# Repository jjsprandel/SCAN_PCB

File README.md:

# 

Welcome to the **SCAN** repository! Below, you will find all the necessary information, from hardware design to software documentation.

---

## GitHub Workflows Status 🔧

Here are the current statuses of our GitHub workflows:

| Workflow Name            | Status                                  |
| ------------------------ | --------------------------------------- |
| **CI - Build**            |  |
| **Docker - Test Build**   |  |

- **CI - Build**: Ensures the project builds successfully.
- **CI - Tests**: Runs all unit and integration tests to ensure everything is working as expected.
- **Docker - Test Build**: Attempts Docker Build upon changes to the Dockerfile.

---

## Table of Contents 📚
- [💡 Overview](#overview)
- [🔧 Hardware Design](#hardware-design)
- [💻 Software](#software)
- [🔨 Build Instructions](#build-instructions)
- [📑 Documentation](#documentation)
- [⚙️ License](#license)

---

## 💡 Overview
 **SCAN** is a low-cost, IoT-driven kiosk system designed to provide real-time analytics based on check-in and check-out information. By integrating NFC-based authentication, real-time data processing, and a user-friendly interface, SCAN provides users with a near-effortless check-in experience and provides facilities with actionable insights for improving operations. SCAN is able to track attendance and provide detailed analytics on occupancy trends, peak usage hours, and visit durations. These insights are accessible to administrator and facility managers via SCAN’s web application, which can provide them with the necessary statistics to allocate resources efficiently, optimize staffing, and improve user experiences.

---

## 🔧 Hardware Design
<details>
  <summary><strong>📡 Schematic</strong></summary>

  Below is the schematic of the hardware design:

  **Key Features**:
  - Feature 1
  - Feature 2
  - Feature 3

  Additional hardware files can be found in the [hardware directory](hardware_design).

</details>

<details>
  <summary><strong>🔌 PCB Design</strong></summary>

  Here's the PCB design layout:

  **Important Notes**:
  - Note about the PCB.
  - Power considerations.
  - Any important design choices.

</details>

---

## 💻 Software
<details>
  <summary><strong>💾 Firmware Overview</strong></summary>

  The firmware is designed to work with the hardware for controlling the device. You can find the code [here](path/to/firmware).

  **Key Libraries Used**:
  - Library 1
  - Library 2

</details>

<details>
  <summary><strong>📦 Installation Guide</strong></summary>

  Follow these steps to install the firmware:
  
  1. Step 1
  2. Step 2
  3. Step 3

  Detailed instructions are available in the [installation guide](link_to_guide).

</details>

---

## 🔨 Build Instructions

<details>
  <summary><strong>🛠️ Build Setup</strong></summary>

  To build the project, follow these steps:

  1. Clone the repository:
     ```bash
     git clone https://github.com/jjsprandel/SCAN.git
     ```
  2. Connect your ESP32 to your computer using USB-C. The Docker container is designed to automatically recognize the device and use port 4000 to communicate to the ESP32 for flashing.
  3. Reopen Visual Studio Code in Container. This step requires having the Docker VS Code extension installed on your host machine. 
  4. Within the container, on first run, configure the ESP-IDF extension from the list of commands that come with the ESP-IDF extension.
     4a. Select "Use existing setup."
     4b. The extension should automatically find the right tool paths and folders. Select the configuration option with the auto-filled paths.
  5. Compile the firmware:
     ```bash
     idf.py build
     ```  
      5a. Alternatively, click the wrench button at the bottom of VS Code to build.
  6. Flash the firmware:
     ```bash
     idf.py --port 'rfc2217://host.docker.internal:4000?ign_set_control' flash
     ```
      6a. Alternatively, click the lightning button at the bottom of VS Code to flash.

  **Tips**:
  - Ensure your system meets the requirements listed in the [build prerequisites](link_to_prerequisites).
  - If you encounter issues, check the [troubleshooting guide](link_to_troubleshooting).

</details>

---

## 📑 Documentation
<details>
  <summary><strong>📝 API Documentation</strong></summary>

  - **[API Reference](link_to_api_reference)**: Detailed API usage and function descriptions.
  - **[Hardware Docs](link_to_hardware_docs)**: Documentation on hardware design.

</details>

<details>
  <summary><strong>📚 Additional Resources</strong></summary>

  - **[Project Wiki](link_to_wiki)**: Explore the project wiki for more in-depth articles.
  - **[User Manual](link_to_user_manual)**: Comprehensive user guide for operation.

</details>

---

## 🔌 Dependencies

This project has the following dependencies that need to be installed:

### **Hardware Dependencies:**
- **KiCad Version**: 8.0.6 (required for schematic and PCB design)
  - Download from [KiCad official website](https://kicad.org/download/).
  
### **Software Dependencies:**
- **USB Drivers**: For proper communication with the hardware, ensure that the appropriate USB drivers are installed.
  - For Windows, you can download and install the **[CP210x USB to UART Bridge VCP drivers](https://www.silabs.com/developer-tools/usb-to-uart-bridge-vcp-drivers?tab=downloads)**.
  - For Linux, you should have the necessary drivers already built into the kernel, but check the [driver documentation](https://www.silabs.com/community/interface/usb-bridges) for troubleshooting.

- **Docker Desktop**: Required to run the ESP-IDF containerized environment.
  - Download from **[Docker Desktop website](https://www.docker.com/products/docker-desktop)**.
  - Follow the installation instructions for your operating system.
  
### **Development Tools:**
- **[Visual Studio Code](https://code.visualstudio.com/)**: Recommended IDE for editing the firmware code.

- **[Git](https://git-scm.com/)**: Version control system.

---

## ⚙️ License
SCAN © 2025 is licensed under Creative Commons Attribution-NonCommercial-NoDerivatives 4.0 International. To view a copy of this license, visit https://creativecommons.org/licenses/by-nc-nd/4.0/ or see the [LICENSE](LICENSE) file.

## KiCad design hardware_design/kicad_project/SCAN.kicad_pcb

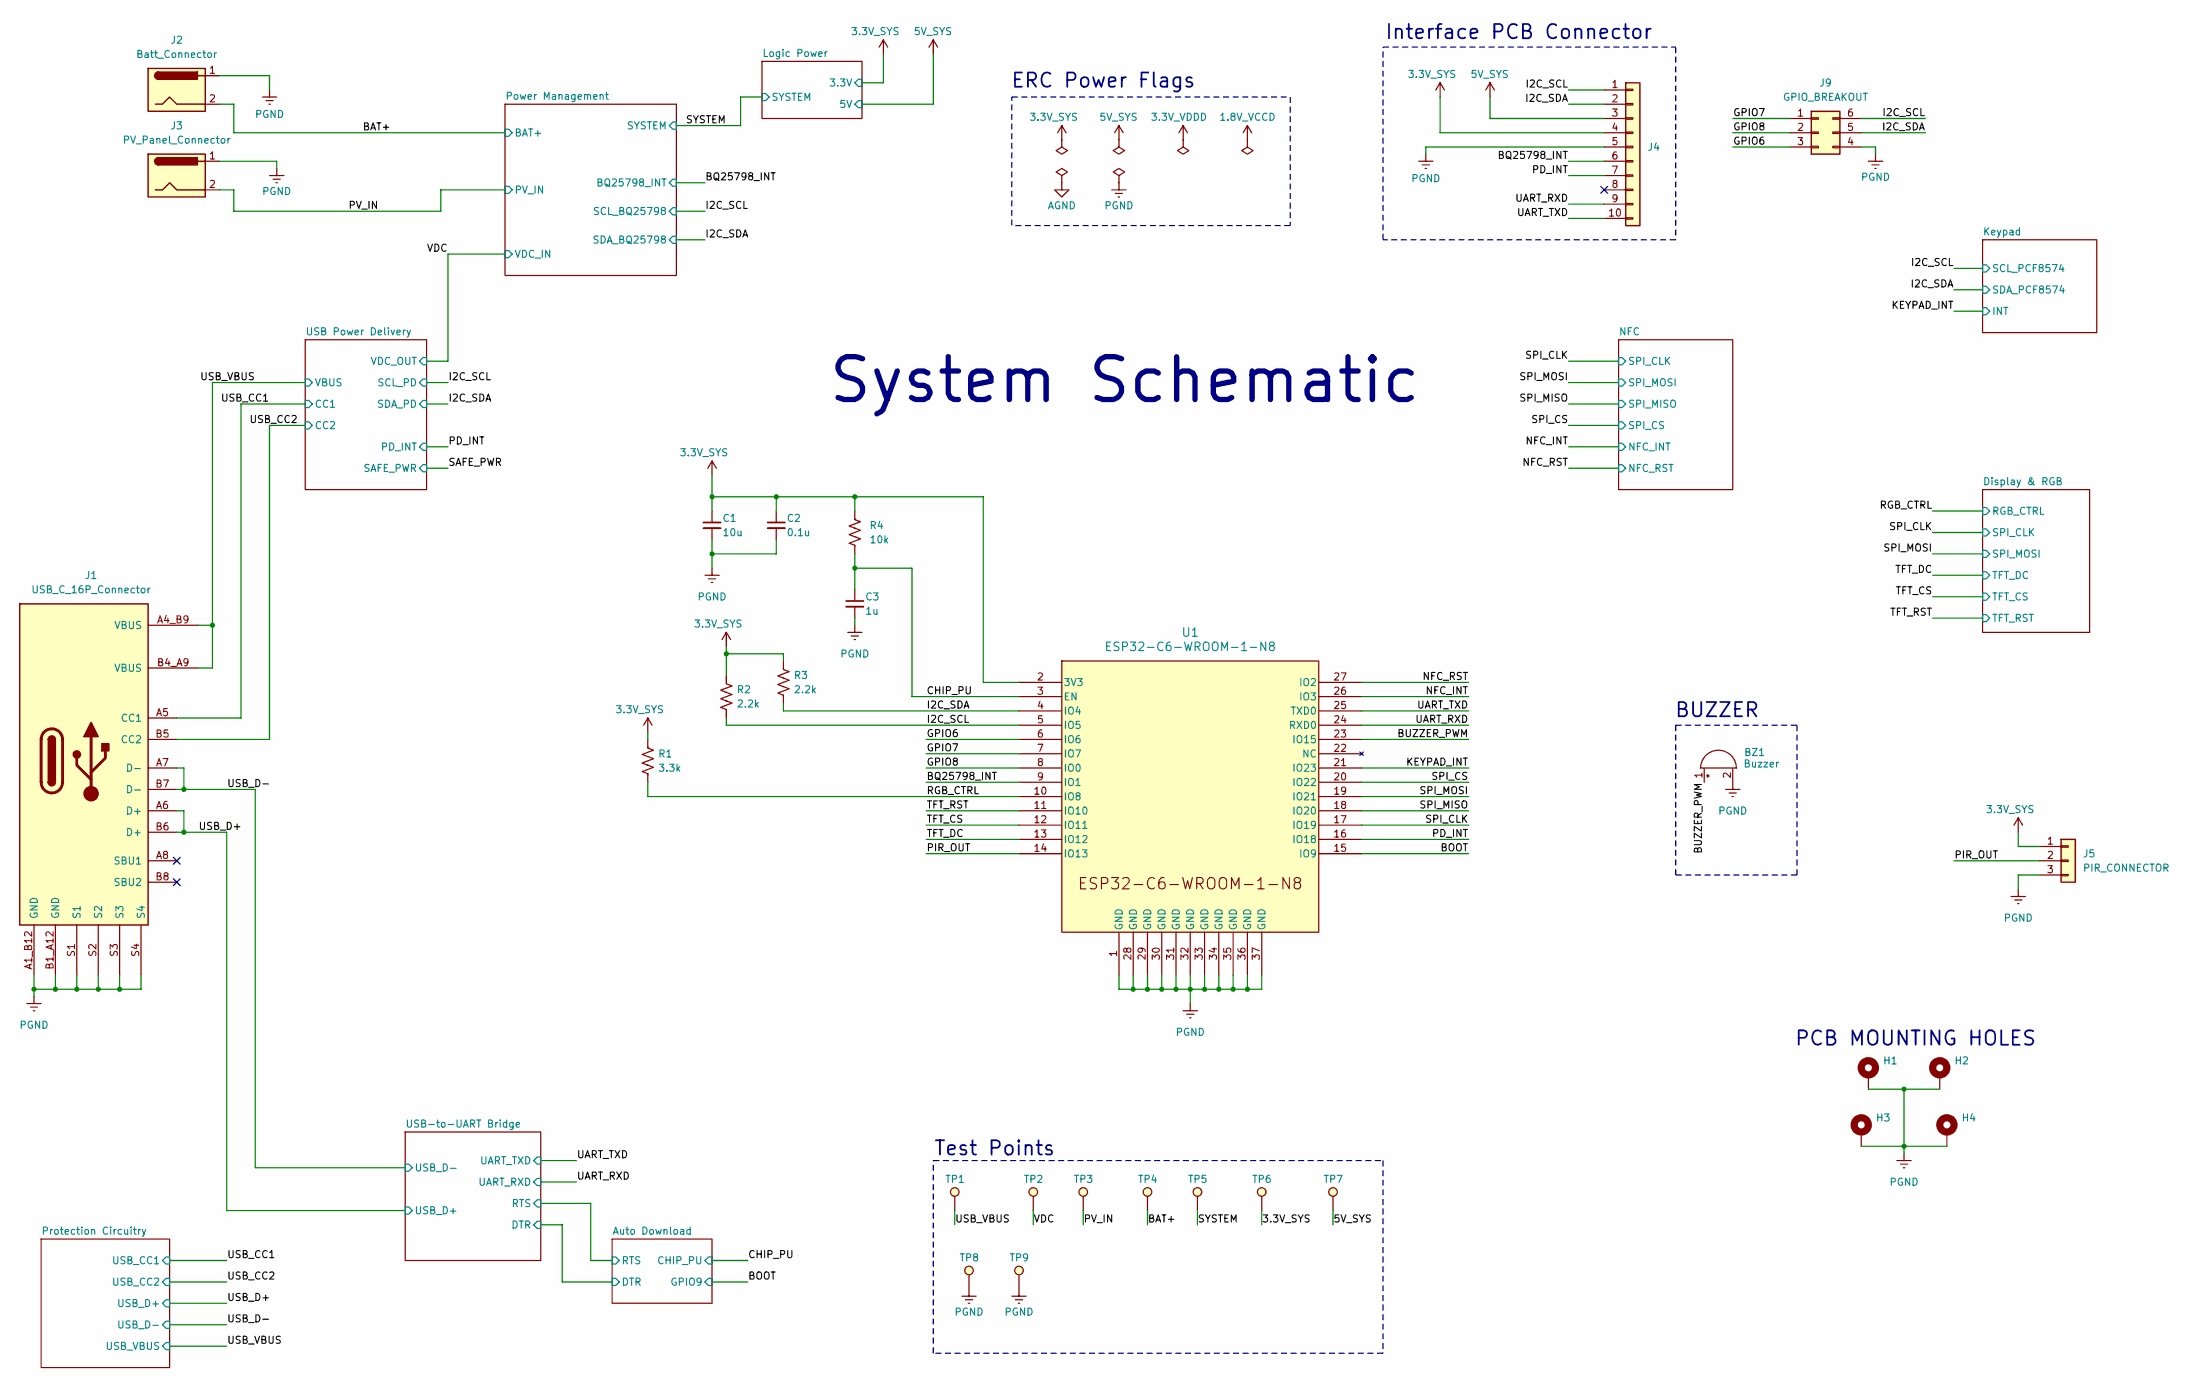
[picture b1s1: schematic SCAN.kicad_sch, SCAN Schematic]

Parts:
BZ1: Buzzer; Buzzer_12x9.5RM7.6
C1: 10u; C_0805_2012Metric; MFR_PN GRM21BZ71E106KE15L; JLCPCB Part Number C237493
C2: 0.1u; C_0402_1005Metric; MFR_PN CC0402KRX7R9BB104; JLCPCB Part Number C131394
C3: 1u; C_0402_1005Metric; MFR_PN GRM155R61E105KA12D; JLCPCB Part Number C77009
H1, H2, H3, H4: MountingHole_Pad; MountingHole_3.2mm_M3_ISO7380_Pad
J1: USB_C_16P_Connector; HRO_TYPE-C-31-M-12; MFR_PN TYPE-C-31-M-12; JLCPCB Part Number C165948
J2: Batt_Connector; TE_282856-2; MFR_PN WJ128V-5.0-2P; JLCPCB Part Number C8269
J3: PV_Panel_Connector; TE_282856-2; MFR_PN WJ128V-5.0-2P; JLCPCB Part Number C8269
J4: Conn_01x10; CONN_SD-43650-001_10_MOL; MFR_PN 0436501000; DigiKey Part Number 23-0436501000-ND
J5: PIR_CONNECTOR; PinHeader_1x03_P2.54mm_Horizontal; MFR_PN A2541WR-3P; JLCPCB Part Number C225489
J9: GPIO_BREAKOUT; PinHeader_2x03_P2.54mm_Horizontal
R1: 3.3k; R_0603_1608Metric; MFR_PN RC0603FR-073K3L; JLCPCB Part Number C108078
R2, R3: 2.2k; R_0805_2012Metric; MFR_PN RC0805FR-072K2L; JLCPCB Part Number C114561
R4: 10k; R_0402_1005Metric; MFR_PN RC0402FR-7W10KL; JLCPCB Part Number C851848
TP1, TP2, TP3, TP4, TP5, TP6, TP7: RED; TP_5010; MFR_PN 5010; JLCPCB Part Number C2906765
TP8, TP9: BLACK; TP_5011; MFR_PN 5011; JLCPCB Part Number C238127
U1: ESP32-C6-WROOM-1-N8; MFR_PN ESP32-C6-WROOM-1-N8; JLCPCB Part Number C5366877

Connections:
3.3V_SYS: C1.1, C2.1, J4.4, J5.1, R1.1, R2.1, R3.1, R4.1, TP6.1, U1.2 (3V3); also elsewhere on the board
5V_SYS: J4.3, TP7.1; also elsewhere on the board
/BAT+: J2.2, TP4.1; also elsewhere on the board
/BOOT: U1.15 (IO9); also elsewhere on the board
/BQ25798_INT: J4.6, U1.9 (IO1); also elsewhere on the board
/BUZZER_PWM: BZ1.1 (-), U1.23 (IO15)
/CHIP_PU: C3.1, R4.2, U1.3 (EN); also elsewhere on the board
/GPIO6: J9.3, U1.6 (IO6)
/GPIO7: J9.1, U1.7 (IO7)
/GPIO8: J9.2, U1.8 (IO0)
/I2C_SCL: J4.1, J9.6, R2.2, U1.5 (IO5); also elsewhere on the board
/I2C_SDA: J4.2, J9.5, R3.2, U1.4 (IO4); also elsewhere on the board
/KEYPAD_INT: U1.21 (IO23); also elsewhere on the board
/NFC_INT: U1.26 (IO3); also elsewhere on the board
/NFC_RST: U1.27 (IO2); also elsewhere on the board
/PD_INT: J4.7, U1.16 (IO18); also elsewhere on the board
/PIR_OUT: J5.2, U1.14 (IO13)
/PV_IN: J3.2, TP3.1; also elsewhere on the board
/RGB_CTRL: R1.2, U1.10 (IO8); also elsewhere on the board
/SPI_CLK: U1.17 (IO19); also elsewhere on the board
/SPI_CS: U1.20 (IO22); also elsewhere on the board
/SPI_MISO: U1.18 (IO20); also elsewhere on the board
/SPI_MOSI: U1.19 (IO21); also elsewhere on the board
/SYSTEM: TP5.1; also elsewhere on the board
/TFT_CS: U1.12 (IO11); also elsewhere on the board
/TFT_DC: U1.13 (IO12); also elsewhere on the board
/TFT_RST: U1.11 (IO10); also elsewhere on the board
/UART_RXD: J4.9, U1.24 (RXD0); also elsewhere on the board
/UART_TXD: J4.10, U1.25 (TXD0); also elsewhere on the board
/USB_CC1: J1.A5 (CC1); also elsewhere on the board
/USB_CC2: J1.B5 (CC2); also elsewhere on the board
/USB_D+: J1.A6 (D+), J1.B6 (D+); also elsewhere on the board
/USB_D-: J1.A7 (D-), J1.B7 (D-); also elsewhere on the board
/USB_VBUS: J1.A4_B9 (VBUS), J1.B4_A9 (VBUS), TP1.1; also elsewhere on the board
/VDC: TP2.1; also elsewhere on the board
PGND: BZ1.2 (+), C1.2, C2.2, C3.2, H1.1, H2.1, H3.1, H4.1, J1.A1_B12 (GND), J1.B1_A12 (GND), J1.S1, J1.S2, J1.S3, J1.S4, J2.1, J3.1, J4.5, J5.3, J9.4, TP8.1, TP9.1, U1.1 (GND), U1.28 (GND), U1.29 (GND), U1.30 (GND), U1.31 (GND), U1.32 (GND), U1.33 (GND), U1.34 (GND), U1.35 (GND), U1.36 (GND), U1.37 (GND); also elsewhere on the board

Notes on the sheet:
Interface PCB Connector
System Schematic
BUZZER
ERC Power Flags
PCB MOUNTING HOLES
Test Points

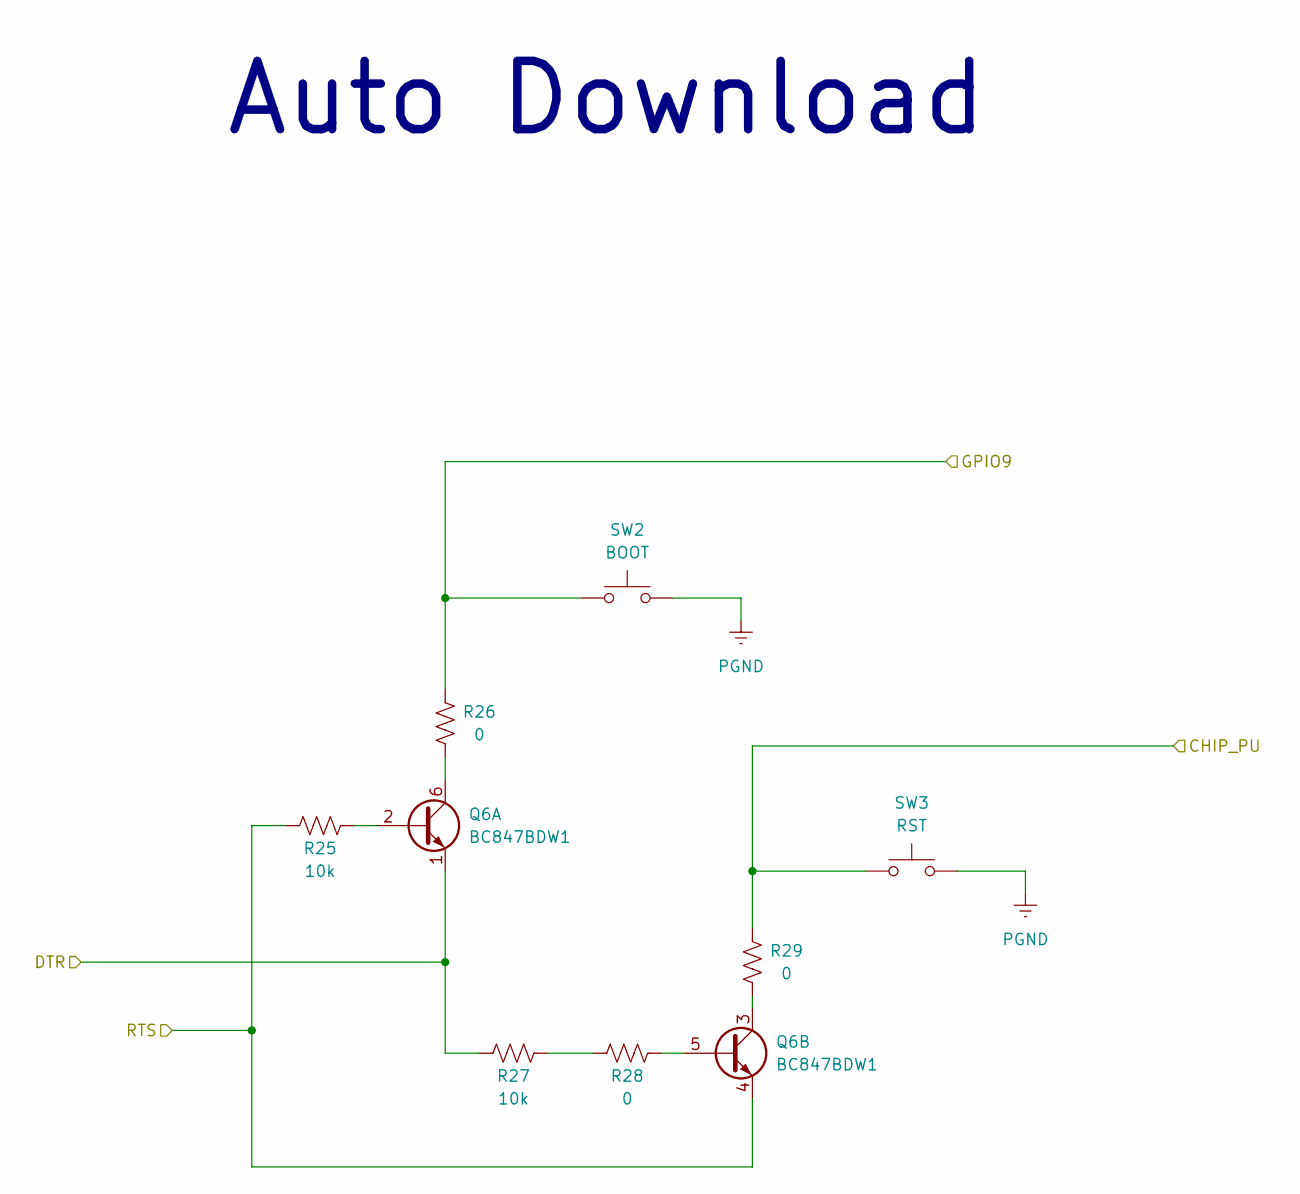
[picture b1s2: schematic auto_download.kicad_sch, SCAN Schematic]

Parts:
Q6: BC847BDW1; SOT-363_SC-70-6; MFR_PN BC847BDW1T1G; JLCPCB Part Number C82368
R25, R27: 10k; R_0805_2012Metric; MFR_PN CRCW080510K0FKEAC; JLCPCB Part Number C844814
R26, R28, R29: 0; R_0805_2012Metric; MFR_PN RC0805JR-070RL; JLCPCB Part Number C96345
SW2: BOOT; SW_SPST_PTS647_Sx38; MFR_PN PTS647SM38SMTR2 LFS; DigiKey Part Number PTS647SM38SMTR2LFSCT-ND
SW3: RST; SW_SPST_PTS647_Sx38; MFR_PN PTS647SM38SMTR2 LFS; DigiKey Part Number PTS647SM38SMTR2LFSCT-ND

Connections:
/Auto Download/DTR: Q6.1 (E1), R27.1; also elsewhere on the board
/Auto Download/RTS: Q6.4 (E2), R25.1; also elsewhere on the board
/BOOT: R26.2, SW2.2; also elsewhere on the board
/CHIP_PU: R29.2, SW3.2; also elsewhere on the board
unnamed: Q6.2 (B1), R25.2
unnamed: Q6.6 (C1), R26.1
unnamed: Q6.5 (B2), R28.2
unnamed: Q6.3 (C2), R29.1
unnamed: R27.2, R28.1
PGND: SW2.1, SW3.1; also elsewhere on the board

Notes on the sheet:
Auto Download

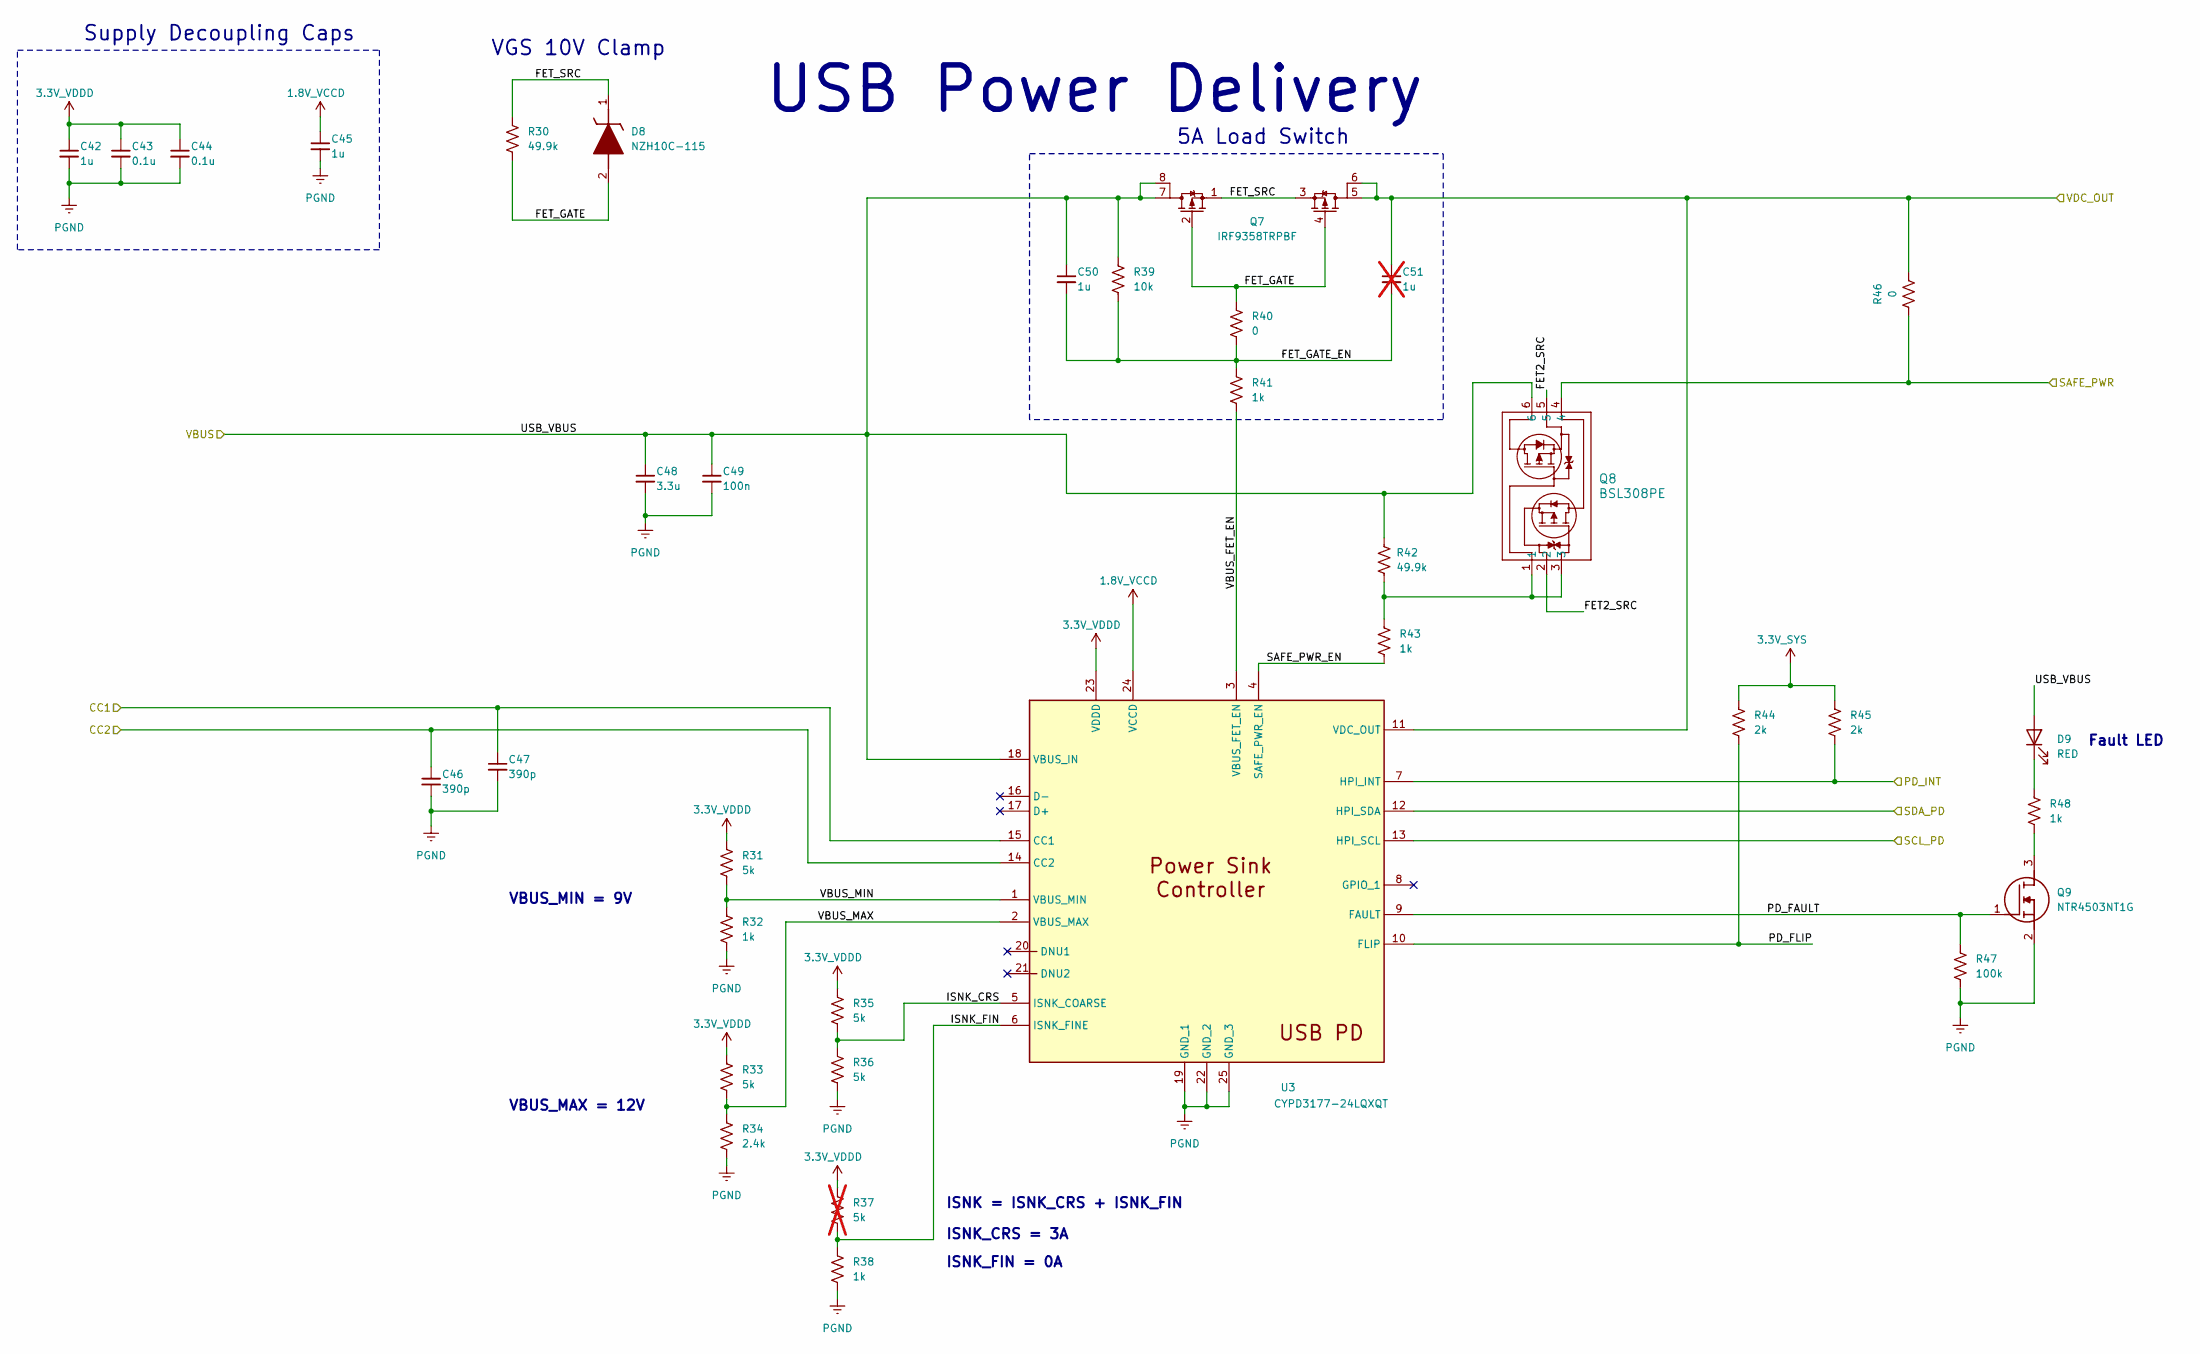
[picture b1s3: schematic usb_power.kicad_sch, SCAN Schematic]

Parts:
C42, C45: 1u; C_0603_1608Metric; MFR_PN GCM188R71C105KA64D; JLCPCB Part Number C161212
C43, C44: 0.1u; C_0402_1005Metric; MFR_PN GRM155R71A104KA01D; JLCPCB Part Number C71687
C46, C47: 390p; C_0603_1608Metric; MFR_PN CC0603JRX7R9BB391; JLCPCB Part Number C519518
C48: 3.3u; C_1210_3225Metric; MFR_PN GRM32DR71H335KA88L; JLCPCB Part Number C397310
C49: 100n; C_0402_1005Metric; MFR_PN GMK105BJ104KV-F; JLCPCB Part Number C187828
C50: 1u; C_0402_1005Metric; MFR_PN CL05A105KL5NRNC; JLCPCB Part Number C307413
C51: 1u; C_0402_1005Metric; MFR_PN C1005X5R1V105K050BC; DigiKey Part Number 445-9073-1-ND; not fitted
D8: NZH10C-115; SODFL3516X120N; Manufacturer_Part_Number NZH10C,115; JLCPCB Part Number C551630
D9: RED; LED_0603_1608Metric; MFR_PN LTST-C190EKT; JLCPCB Part Number C364560
Q7: IRF9358TRPBF; SO8_IRF9358TRPBF_INF; Manufacturer_Part_Number DMP3056LSD-13; JLCPCB Part Number C537847
Q8: BSL308PE; PG-TSOP6-6-4_INF; MFR_PN BSL308PEH6327XTSA1; DigiKey Part Number BSL308PEH6327XTSA1CT-ND
Q9: NTR4503NT1G; SOT23_318-08_ONS; MFR_PN NTR4503NT1G; JLCPCB Part Number C94763
R30, R42: 49.9k; R_0402_1005Metric; MFR_PN RK73H1ETTP4992F; JLCPCB Part Number C173335
R31, R33, R35, R36: 5k; R_0603_1608Metric; MFR_PN CRCW06034K99FKEA; JLCPCB Part Number C844793
R32, R38, R48: 1k; R_0603_1608Metric; MFR_PN CRCW06031K00FKEA; JLCPCB Part Number C844920
R34: 2.4k; R_0603_1608Metric; MFR_PN ERJ-3GEYJ242V; JLCPCB Part Number C403460
R37: 5k; R_0603_1608Metric; MFR_PN CRCW06034K99FKEA; JLCPCB Part Number C844793; not fitted
R39: 10k; R_0402_1005Metric; MFR_PN RC0402JR-0710KL; JLCPCB Part Number C60489
R40: 0; R_0402_1005Metric; MFR_PN RC0402FR-070RL; JLCPCB Part Number C106231
R41, R43: 1k; R_0402_1005Metric; MFR_PN RC0402JR-071KL; JLCPCB Part Number C105637
R44, R45: 2k; R_0805_2012Metric; MFR_PN RC0805JR-072KL; JLCPCB Part Number C114748
R46: 0; R_0805_2012Metric; MFR_PN PA0805JR-470RL; JLCPCB Part Number C858567
R47: 100k; R_0805_2012Metric; MFR_PN ERJ-P06F1003V; JLCPCB Part Number C441992
U3: CYPD3177-24LQXQT; QFN50P400X400X60-25N-D; Manufacturer_Part_Number CYPD3177-24LQXQ; JLCPCB Part Number C2952489

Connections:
1.8V_VCCD: C45.1, U3.24 (VCCD)
3.3V_SYS: R44.1, R45.1; also elsewhere on the board
3.3V_VDDD: C42.1, C43.1, C44.1, R31.1, R33.1, R35.1, R37.1, U3.23 (VDDD)
/I2C_SCL: U3.13 (HPI_SCL); also elsewhere on the board
/I2C_SDA: U3.12 (HPI_SDA); also elsewhere on the board
/PD_INT: R45.2, U3.7 (HPI_INT); also elsewhere on the board
/SAFE_PWR: Q8.4, R46.1
/USB Power Delivery/FET2_SRC: Q8.2, Q8.5
/USB Power Delivery/FET_GATE: D8.2 (A), Q7.2 (G1), Q7.4 (G2), R30.2, R40.1
/USB Power Delivery/FET_GATE_EN: C50.2, C51.2, R39.2, R40.2, R41.1
/USB Power Delivery/FET_SRC: D8.1 (K), Q7.1 (S1), Q7.3 (S2), R30.1
/USB Power Delivery/ISNK_CRS: R35.2, R36.1, U3.5 (ISNK_COARSE)
/USB Power Delivery/ISNK_FIN: R37.2, R38.1, U3.6 (ISNK_FINE)
/USB Power Delivery/PD_FAULT: Q9.1 (G), R47.1, U3.9 (FAULT)
/USB Power Delivery/PD_FLIP: R44.2, U3.10 (FLIP)
/USB Power Delivery/SAFE_PWR_EN: R43.2, U3.4 (SAFE_PWR_EN)
/USB Power Delivery/VBUS_FET_EN: R41.2, U3.3 (VBUS_FET_EN)
/USB Power Delivery/VBUS_MAX: R33.2, R34.1, U3.2 (VBUS_MAX)
/USB Power Delivery/VBUS_MIN: R31.2, R32.1, U3.1 (VBUS_MIN)
/USB_CC1: C47.1, U3.15 (CC1); also elsewhere on the board
/USB_CC2: C46.1, U3.14 (CC2); also elsewhere on the board
/USB_VBUS: C48.1, C49.1, C50.1, D9.2 (A), Q7.7 (D1_1), Q7.8 (D1_2), Q8.6, R39.1, R42.1, U3.18 (VBUS_IN); also elsewhere on the board
/VDC: C51.1, Q7.5 (D2_1), Q7.6 (D2_2), R46.2, U3.11 (VDC_OUT); also elsewhere on the board
unnamed: D9.1 (K), R48.1
unnamed: Q8.1, Q8.3, R42.2, R43.1
unnamed: Q9.3 (D), R48.2
PGND: C42.2, C43.2, C44.2, C45.2, C46.2, C47.2, C48.2, C49.2, Q9.2 (S), R32.2, R34.2, R36.2, R38.2, R47.2, U3.19 (GND_1), U3.22 (GND_2), U3.25 (GND_3); also elsewhere on the board

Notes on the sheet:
ISNK_CRS = 3A
VGS 10V Clamp
5A Load Switch
USB Power Delivery
Fault LED
ISNK = ISNK_CRS + ISNK_FIN
VBUS_MAX = 12V
Supply Decoupling Caps
VBUS_MIN = 9V
ISNK_FIN = 0A

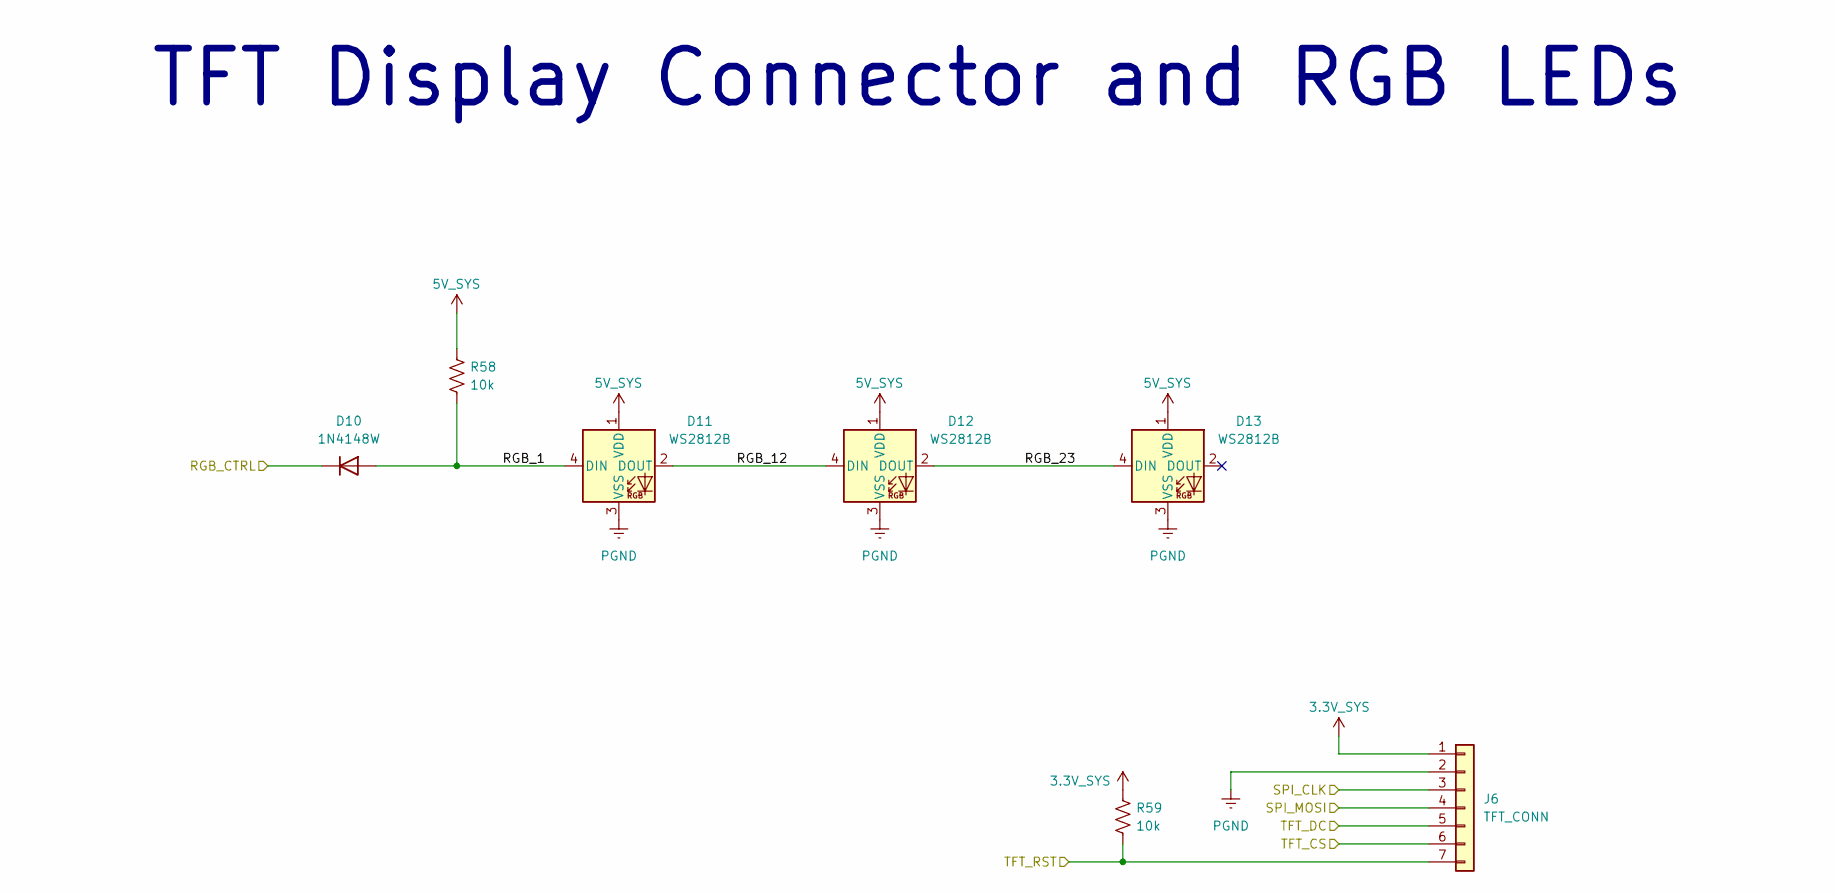
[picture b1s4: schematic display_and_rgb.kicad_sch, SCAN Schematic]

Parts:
D10: 1N4148W; D_SOD-123; MFR_PN 1N4448W; JLCPCB Part Number C8601
D11, D12, D13: WS2812B; LED_WS2812B_PLCC4_5.0x5.0mm_P3.2mm; MFR_PN COM-16347; JLCPCB Part Number C7433145
J6: TFT_CONN; PinHeader_1x07_P2.54mm_Horizontal
R58, R59: 10k; R_0805_2012Metric; MFR_PN CRCW080510K0FKEAC; JLCPCB Part Number C844814

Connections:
3.3V_SYS: J6.1, R59.1; also elsewhere on the board
5V_SYS: D11.1 (VDD), D12.1 (VDD), D13.1 (VDD), R58.1; also elsewhere on the board
/Display & RGB/RGB_1: D10.2 (A), D11.4 (DIN), R58.2
/Display & RGB/RGB_12: D11.2 (DOUT), D12.4 (DIN)
/Display & RGB/RGB_23: D12.2 (DOUT), D13.4 (DIN)
/RGB_CTRL: D10.1 (K); also elsewhere on the board
/SPI_CLK: J6.3; also elsewhere on the board
/SPI_MOSI: J6.4; also elsewhere on the board
/TFT_CS: J6.6; also elsewhere on the board
/TFT_DC: J6.5; also elsewhere on the board
/TFT_RST: J6.7, R59.2; also elsewhere on the board
PGND: D11.3 (VSS), D12.3 (VSS), D13.3 (VSS), J6.2; also elsewhere on the board

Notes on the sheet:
TFT Display Connector and RGB LEDs

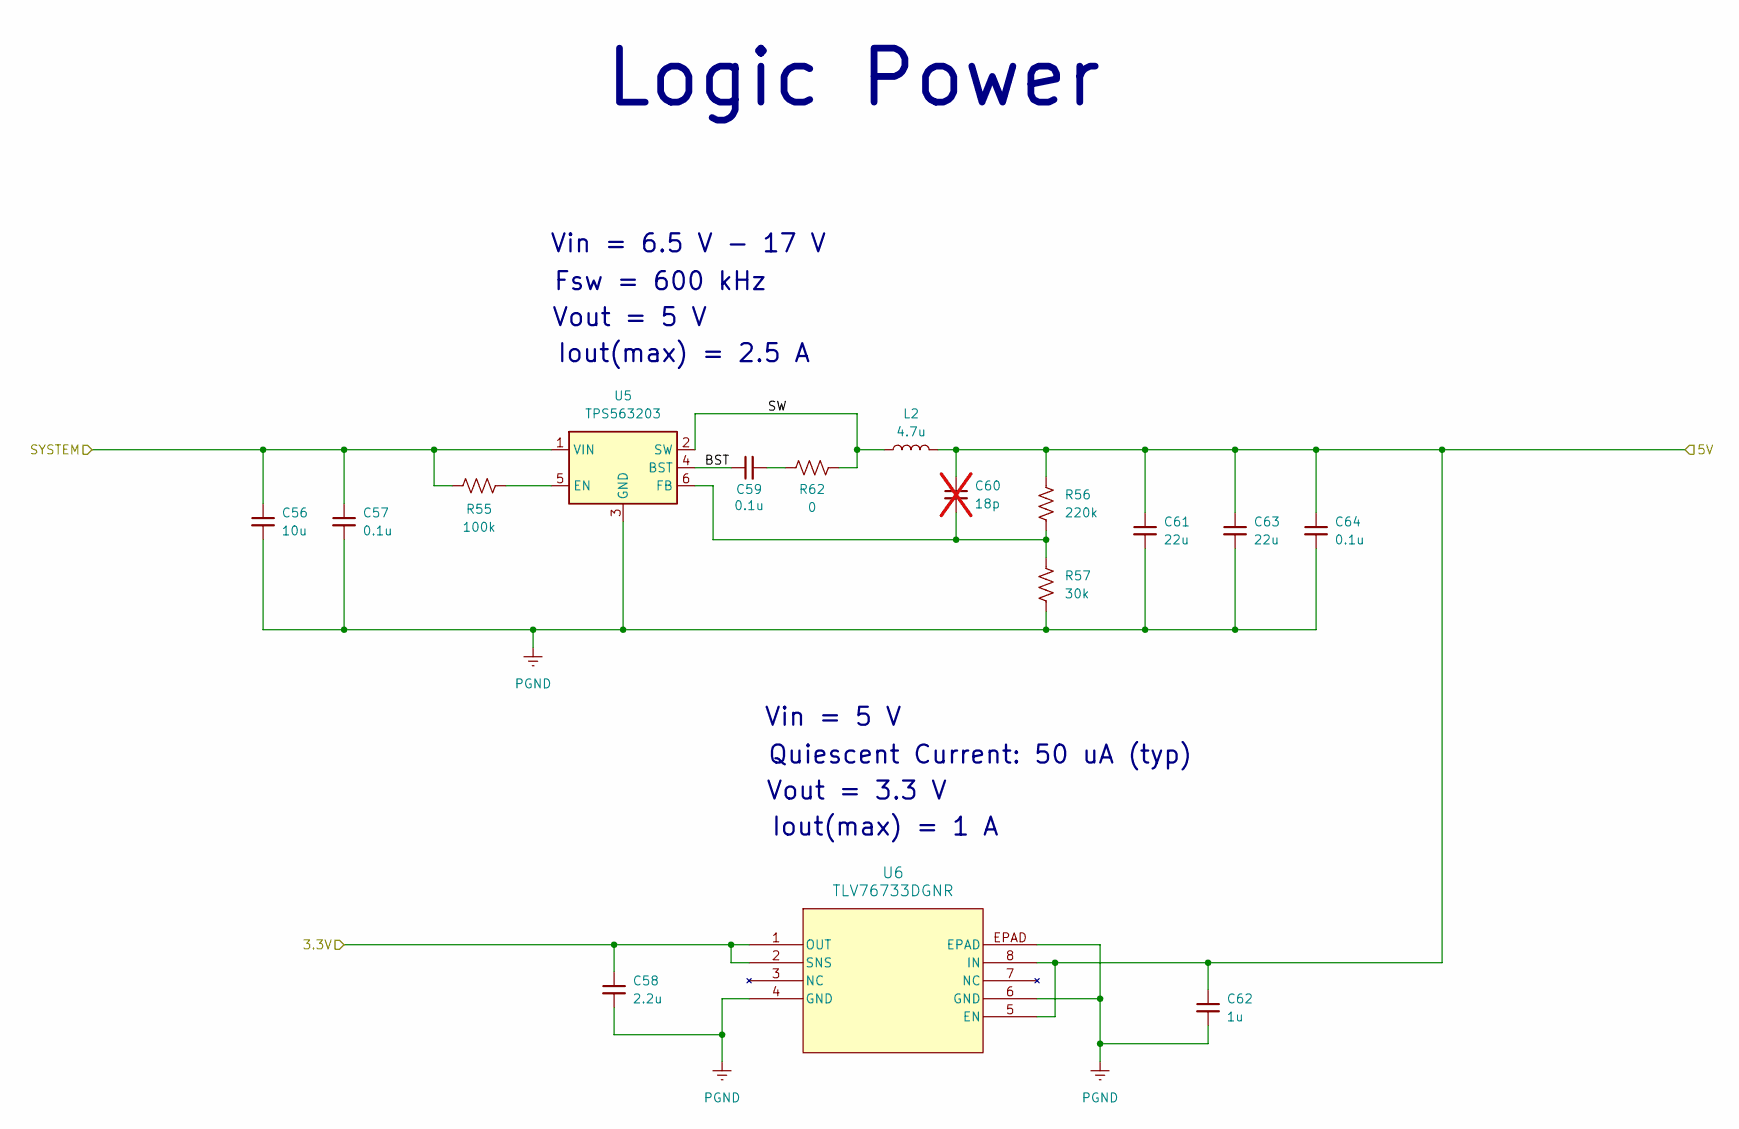
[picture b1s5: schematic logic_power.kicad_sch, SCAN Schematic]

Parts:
C56: 10u; C_0805_2012Metric; MFR_PN GRM21BR61E106MA73L; JLCPCB Part Number C391262
C57, C59, C64: 0.1u; C_0603_1608Metric; MFR_PN CC0603KRX7R9BB104; JLCPCB Part Number C14663
C58: 2.2u; C_0805_2012Metric; MFR_PN CC0805KKX7R9BB225; JLCPCB Part Number C125847
C60: 18p; C_0603_1608Metric; not fitted
C61, C63: 22u; C_0805_2012Metric; MFR_PN GRM21BR61A226ME44L; JLCPCB Part Number C441864
C62: 1u; C_0805_2012Metric; MFR_PN CC0805KKX7R9BB105; JLCPCB Part Number C91185
L2: 4.7u; WE-LHMI_7030_705048; MFR_PN 74437349047; JLCPCB Part Number C6404631
R55: 100k; R_0603_1608Metric; MFR_PN CRCW0603100KJNEA; JLCPCB Part Number C844723
R56: 220k; R_0603_1608Metric; MFR_PN RC0603FR-07220KL; JLCPCB Part Number C123420
R57: 30k; R_0603_1608Metric; MFR_PN RC0603FR-0730KL; JLCPCB Part Number C100001
R62: 0; R_0603_1608Metric; MFR_PN CRCW06030000Z0EA; JLCPCB Part Number C844915
U5: TPS563203; SOT-563; MFR_PN TPS563203DRLR; JLCPCB Part Number C22445512
U6: TLV76733DGNR; VSSOP8_DGN_TEX; MFR_PN TLV76733DGNR; JLCPCB Part Number C2873382

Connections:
3.3V_SYS: C58.1, U6.1 (OUT), U6.2 (SNS); also elsewhere on the board
5V_SYS: C60.1, C61.1, C62.1, C63.1, C64.1, L2.2, R56.1, U6.5 (EN), U6.8 (IN); also elsewhere on the board
/Logic Power/BST: C59.1, U5.4 (BST)
/Logic Power/SW: L2.1, R62.2, U5.2 (SW)
/SYSTEM: C56.1, C57.1, R55.1, U5.1 (VIN); also elsewhere on the board
unnamed: C59.2, R62.1
unnamed: R55.2, U5.5 (EN)
unnamed: C60.2, R56.2, R57.1, U5.6 (FB)
PGND: C56.2, C57.2, C58.2, C61.2, C62.2, C63.2, C64.2, R57.2, U5.3 (GND), U6.4 (GND), U6.6 (GND), U6.EPAD; also elsewhere on the board

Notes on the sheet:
Iout(max) = 2.5 A
Vin = 5 V
Vout = 3.3 V
Quiescent Current: 50 uA (typ)
Vin = 6.5 V - 17 V
Logic Power
Fsw = 600 kHz
Vout = 5 V
Iout(max) = 1 A

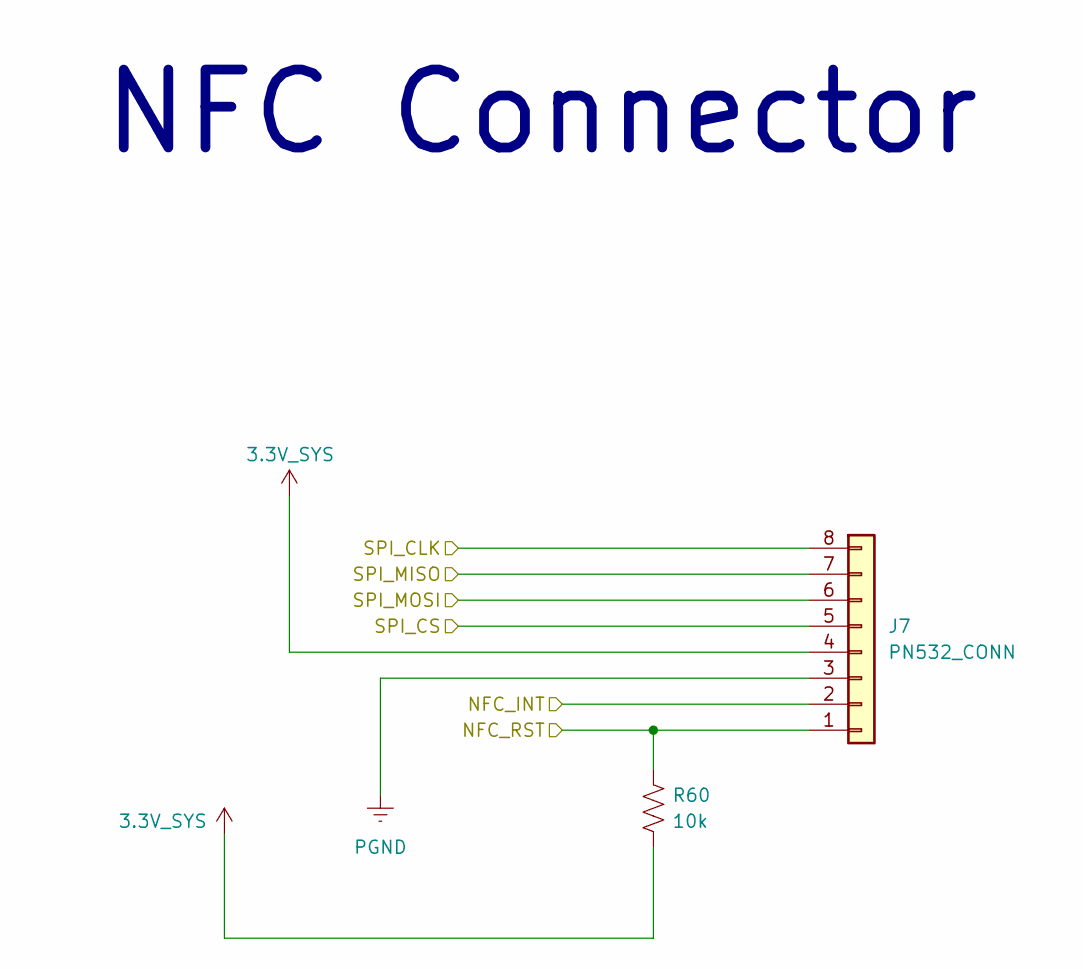
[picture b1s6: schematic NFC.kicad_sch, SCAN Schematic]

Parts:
J7: PN532_CONN; PinHeader_1x08_P2.54mm_Horizontal
R60: 10k; R_0805_2012Metric; MFR_PN CRCW080510K0FKEAC; JLCPCB Part Number C844814

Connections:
3.3V_SYS: J7.4 (Pin_5), R60.2; also elsewhere on the board
/NFC_INT: J7.2 (Pin_7); also elsewhere on the board
/NFC_RST: J7.1 (Pin_8), R60.1; also elsewhere on the board
/SPI_CLK: J7.8 (Pin_1); also elsewhere on the board
/SPI_CS: J7.5 (Pin_4); also elsewhere on the board
/SPI_MISO: J7.7 (Pin_2); also elsewhere on the board
/SPI_MOSI: J7.6 (Pin_3); also elsewhere on the board
PGND: J7.3 (Pin_6); also elsewhere on the board

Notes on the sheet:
NFC Connector
